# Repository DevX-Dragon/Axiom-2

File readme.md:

# Axiom-2 🤖🖊️
YO. Welcome to Axiom-2. It’s a CNC drawing machine that basically does my homework (not really, don't tell my teacher). I built this because I wanted a robot that draws better than me.

## What is this?
It’s a "Drawing Bot" that uses an Arduino Uno and a CNC Shield to move a pen around. It runs on GRBL (which is basically the brain) with some tiny tweaks I made so it doesn't freak out.

## Images
### Full Render

(still in prodcution so not fully rendered)

### Belt Diagrams

### CNC Overview

## Cool Stuff Inside
**The Brain:** Arduino Uno + CNC Shield (v3)

**Firmware:** GRBL (hacked a bit)

**The Parts:** I put the BOM (Bill of Materials) in the .xlsx file above. It has all the nuts, bolts, and rods you need to buy.

**Pictures:** Check the /images folder to see what it actually looks like.

## How to use it (I think)
**Flash it:** Get the GRBL firmware onto the Arduino.

**Wire it:** Plug the stepper motors into the shield. Don't blow it up.

**Software:** Use something like Universal Gcode Sender (UGS) to send your drawings to the bot.

**Draw:** Put a pen in the holder and watch it go zoom.

## Hardware
I put the CAD files/designs in the /hardware folder. If you have a 3D printer, you can probably make this yourself.

## 🛠️ Axiom-2 Official BOM (with links!!)

| Product Name | Qty | Price (ea) | Total | Notes |
| :--- | :---: | :--- | :--- | :--- |
| [**Nema 17 Stepper Motor**](https://www.duino.lk/product/nema-17-stepper-motor-bipolar-1-8deg-1-5a-42ncm-42x42x40mm/) | 2 | $8.07 | $16.14 | Bipolar version |
| [**Linear Rod M8 (1m)**](https://www.duino.lk/product/1000mm-8mm-smooth-shaft/) | 2 | $5.81 | $11.62 | Need 2x 450mm and 2x 350mm |
| **Linear Rod 3mm** | 2 | - | $0.00 | Salvaging from a CDROM |
| **Threaded Rod M8 x 480mm** | 1 | - | $0.00 | Still haven't found a link for this |
| [**LM8UU Bearings**](https://www.duino.lk/product/lm8luu-lm20luu-ball-bearings/) | 8 | $1.45 | $11.60 | Standard sliders |
| [**SG90 Servo Motor**](https://www.duino.lk/product/servo-motor-sg90-9g-micro-servo-motor/) | 1 | $1.81 | $1.81 | Pen lift go brrrr |
| **Spring** | 1 | - | $0.00 | From a ballpoint pen lol |
| [**GT2 Pulley (16T)**](https://www.duino.lk/product/gt2-16t-16-teeth-5mm-bore/) | 2 | $0.97 | $1.94 | 5mm bore |
| [**Bearing 624zz**](https://www.duino.lk/product/624zz-ball-bearing/) | 5 | $0.48 | $2.40 | Tiny bearings |
| [**GT2 Belt (1m)**](https://www.duino.lk/product/gt2-6mm-width-2gt-pu-transmission-timing-belt/) | 2 | $1.61 | $3.22 | Buying 2m total |
| [**CNC Shield + Uno + Drivers**](https://www.duino.lk/product/cnc-shield-v3-0-uno-r3-4pcs-a4988-drivers/) | 1 | $20.97 | $20.97 | Cheaper as a kit |
| [**Jumper Connectors**](https://www.duino.lk/product/2-pin-jumper-connector-stud-2-54mm-standard/) | 1 | $0.32 | $0.32 | |
| [**12V 2A Power Supply**](https://www.duino.lk/product/power-supply-adapter-3-pin-ac-dc-12v-2a/) | 1 | $2.42 | $2.42 | |
| **3D Printing (Legion)** | 1 | $30.00 | $30.00 | |
| **Exchange Tax** | - | - | $5.00 | |
| **Shipping** | - | - | $5.00 | |
| **TOTAL** | | | **$112.44** | |
> (THIS IS USING A LOCAL ONLY ELECTRONICS STORE. IF YOU'RE GOING TO HAVE TO SOURCE IT YOURSELF. USE AMAZON , ALIEXPRESS , TEMU)
> THERE ARE STILL NUTS , WASHERS , ETC YOU NEED BUY SEPERATELY

Made by DevX-Dragon 🐉
(If it breaks, its not my fault lol)

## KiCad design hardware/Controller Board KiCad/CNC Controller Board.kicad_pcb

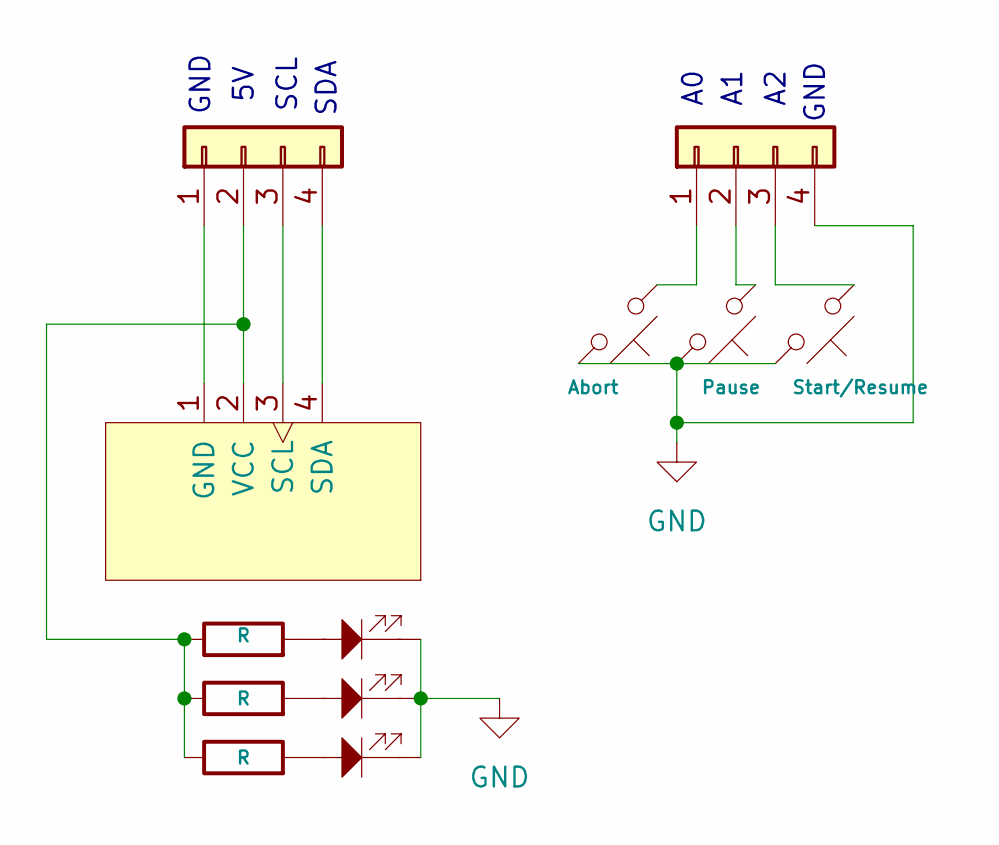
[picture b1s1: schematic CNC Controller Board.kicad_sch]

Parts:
D1, D2, D3: LED; LED_D3.0mm
J1, J2: Conn_01x04; TerminalBlock_Phoenix_PT-1,5-4-3.5-H_1x04_P3.50mm_Horizontal
J4: OLED_128x64
R1, R2, R3: R; R_Axial_DIN0207_L6.3mm_D2.5mm_P7.62mm_Horizontal
SW1: Abort; SW_PUSH_6mm
SW2: Pause; SW_PUSH_6mm
SW3: Start/Resume; SW_PUSH_6mm

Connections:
GND: D1.1, D2.1, D3.1, J2.4, SW1.2, SW2.2, SW3.2
unnamed: D1.2, R1.2
unnamed: D2.2, R2.2
unnamed: D3.2, R3.2
unnamed: J1.1, J4.1 (GND)
unnamed: J1.2, J4.2 (VCC), R1.1, R2.1, R3.1
unnamed: J1.3, J4.3 (SCL)
unnamed: J1.4, J4.4 (SDA)
unnamed: J2.1, SW1.1
unnamed: J2.2, SW2.1
unnamed: J2.3, SW3.1

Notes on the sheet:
SCL
GND
SDA

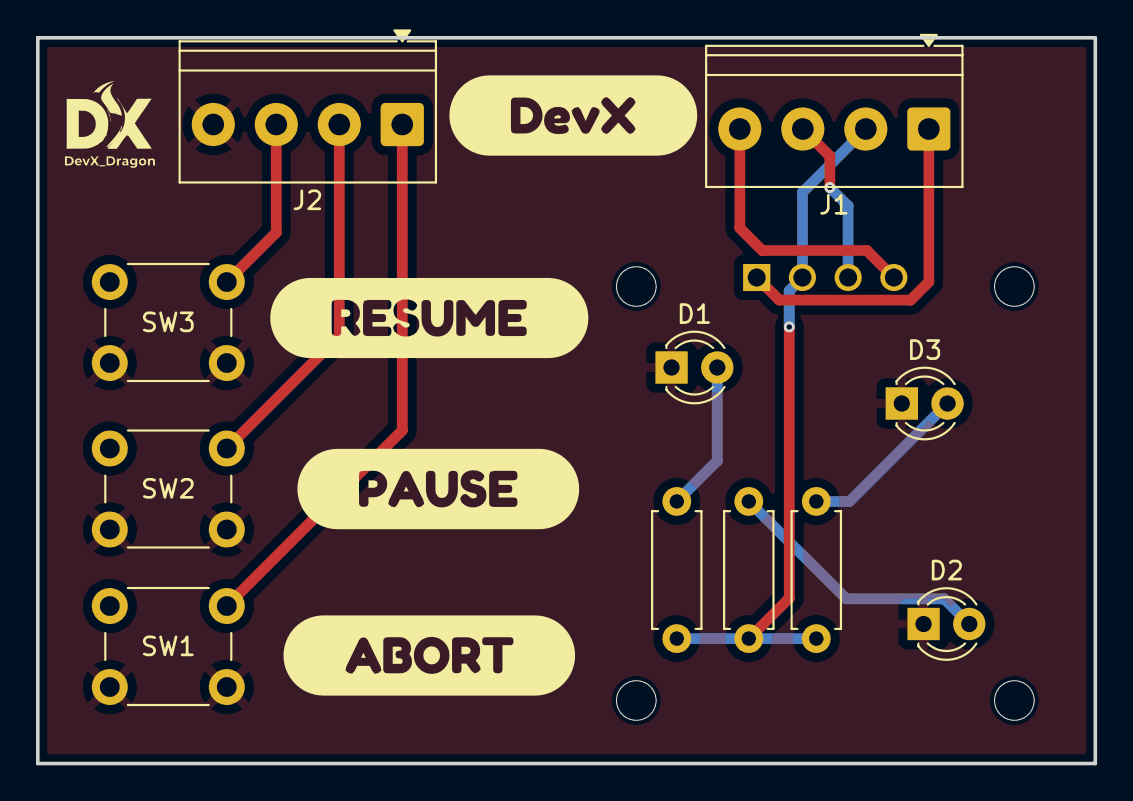
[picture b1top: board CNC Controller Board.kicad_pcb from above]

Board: 2 copper layers, 58.8 x 40.3 mm, 17 parts (1 on the bottom side), 11 nets.

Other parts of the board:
kibuzzard-69997A6C: G***; kibuzzard-69997A6C
kibuzzard-699976DE: G***; kibuzzard-699976DE
kibuzzard-699976F2: G***; kibuzzard-699976F2
kibuzzard-699976FE: G***; kibuzzard-699976FE
kibuzzard-699979CF: G***; kibuzzard-699979CF

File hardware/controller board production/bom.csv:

Designator,Footprint,Quantity,Value,LCSC Part #
"D1, D2, D3",LED_D3.0mm,3,LED,
"J1, J2","TerminalBlock_Phoenix_PT-1,5-4-3.5-H_1x04_P3.50mm_Horizontal",2,Conn_01x04,
J4,OLED_128x64,1,OLED_128x64,
"R1, R2, R3",R_Axial_DIN0207_L6.3mm_D2.5mm_P7.62mm_Horizontal,3,R,
SW1,SW_PUSH_6mm,1,Abort,
SW2,SW_PUSH_6mm,1,Pause,
SW3,SW_PUSH_6mm,1,Start/Resume,

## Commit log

2026-02-18 Axiom-2: Initial Build
2026-02-18 Uploading Images
2026-02-18 Uploading the missing .step file
2026-02-20 Initial BOM push v1
2026-02-20 BOM Upload
2026-02-20 BOMv1 TO ROOT DIR
2026-02-20 initial image upload
2026-02-20 Added some firmware tweals , servo motor needs a special firmware edit as well
2026-02-21 Firmware Upload v1
2026-02-21 Adding Controller PCB Files
2026-02-21 BOM Modifcations for PCB
